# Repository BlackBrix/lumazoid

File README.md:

# Lumazoid

Firmware for the Lumazoid realtime music visualizer board from nootropic design.
Detailed technical information about Lumazoid is at http://nootropicdesign.com/lumazoid  
  
Shop: https://nootropicdesign.com/store/product-category/led-controllers/  
  
Install libraries/ffft in your Arduino sketchbook libraries folder.

Requires the [Adafruit NeoPixel library](https://github.com/adafruit/Adafruit_NeoPixel). 
Your directory structure should look like this:

```
your_sketchbook
 |
 +--libraries
 |   |
 |   +--ffft
 |   |
 |   +--Adafruit_NeoPixel
 |
 +--Lumazoid
     |
     +--Lumazoid.h
     +--Lumazoid.ino
```

In the Arduino IDE, select board type "Arduino Uno" to upload to the Lumazoid.  
  
https://youtu.be/Vjp7iLEZsX4  
https://youtu.be/2BDE81b42Ac  
https://youtu.be/lYz1uqOQcGg  
https://youtu.be/453p5HPAYZY  
https://youtu.be/N-TBdfP13BE  
  
Forum:  
https://nootropicdesign.com/store/forums/

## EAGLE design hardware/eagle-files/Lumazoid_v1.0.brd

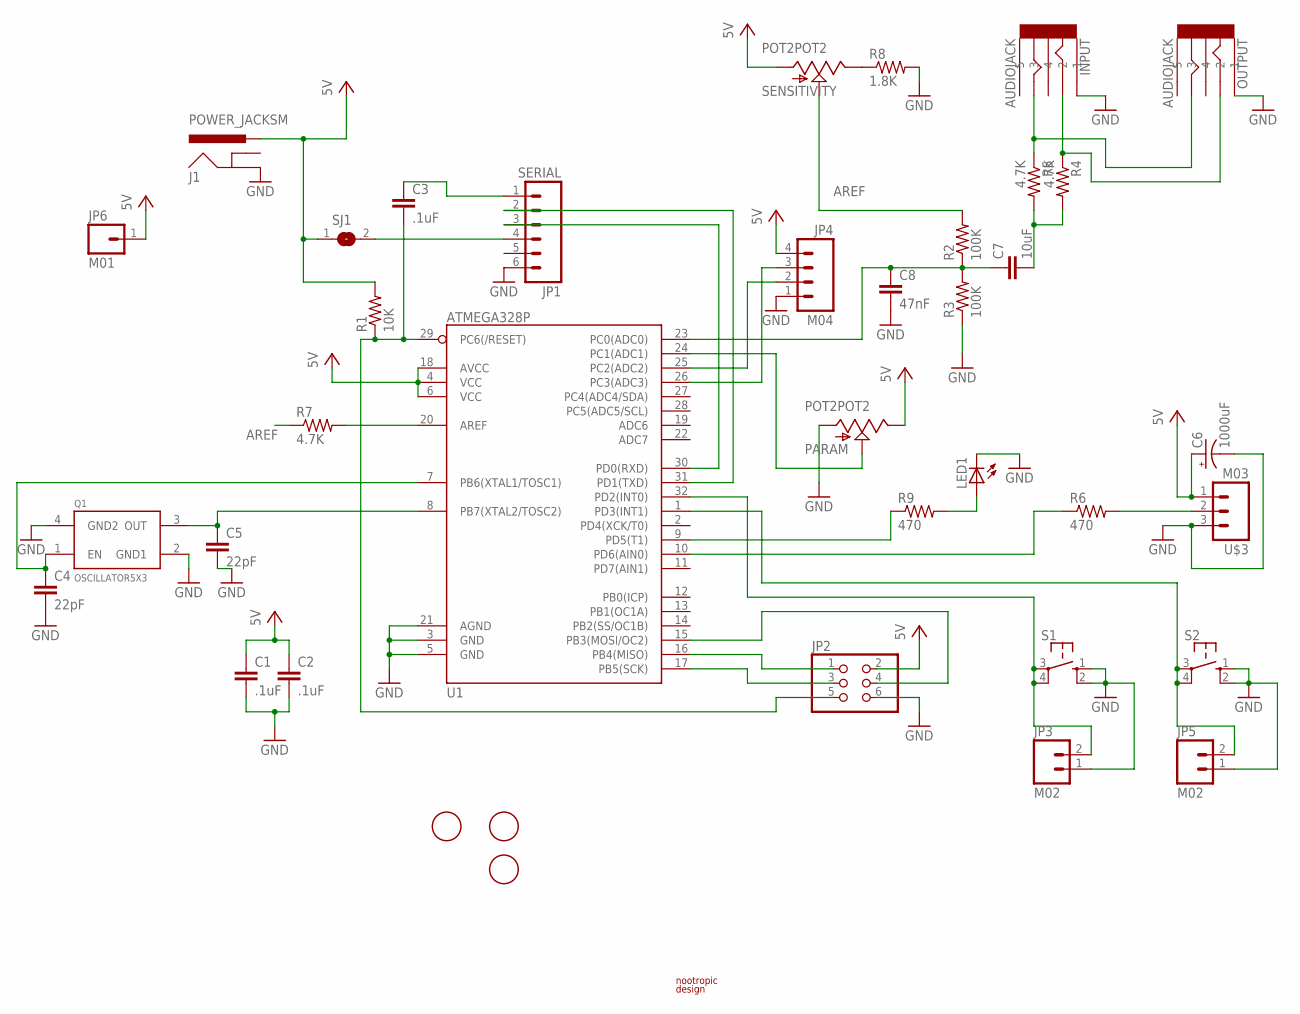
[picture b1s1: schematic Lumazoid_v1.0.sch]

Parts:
C1, C2, C3: .1uF; C0603
C4, C5: 22pF; C0603
C6: 1000uF; E5-10,5
C7: 10uF; C1206
C8: 47nF; C0603
FID1, FID2, FID3: FIDUCIAL; FIDUCIAL_1MM
INPUT: AUDIOJACK
J1: POWER_JACKSM; POWER_JACK_SM
JP1: SERIAL; 1X06
JP2: PINHD-2X3; 2X03
JP3, JP5: M02; 1X02
JP4: M04; 1X04
JP6: M01; 1X01
LED1: LEDCHIPLED_0805; CHIPLED_0805
OUTPUT: AUDIOJACK
PARAM: POT2POT2; ALPS_POT
Q1: OSCILLATOR5X3; CRYSTAL-SMD-5X3
R1: 10K; R0603
R2, R3: 100K; R0603
R4, R5, R7: 4.7K; R0603
R6, R9: 470; R0603
R8: 1.8K; R0603
S1, S2: SWITCH-TACT6MMSMT-J; DTSM-6-JBEND
SENSITIVITY: POT2POT2; ALPS_POT
SJ1: SJ
U1: ATMEGA328P; TQFP32-08
U$1: LOGO; LOGO_SMALL
U$3: M03; 1X03

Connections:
A0: C7.1, C8.1, R2.1, R3.2, U1.23 (PC0(ADC0))
A1: PARAM.P$2 (2), U1.24 (PC1(ADC1))
A2: JP4.2, U1.25 (PC2(ADC2))
A3: JP4.3, U1.26 (PC3(ADC3))
AREF: R2.2, R7.1, SENSITIVITY.P$2 (2)
D1: JP5.2, S2.3, S2.4 (P1), U1.1 (PD3(INT1))
D2: JP3.2, S1.3, S1.4 (P1), U1.32 (PD2(INT0))
DTR: C3.1, JP1.1
GND: C1.2, C2.2, C4.2, C5.2, C6.-, C8.2, INPUT.1, J1.GND, JP1.6, JP2.6, JP3.1, JP4.1, JP5.1, LED1.C, OUTPUT.1, PARAM.P$1 (1), Q1.2 (GND1), Q1.4 (GND2), R3.1, R8.2, S1.1 (S), S1.2 (S1), S2.1 (S), S2.2 (S1), U1.3 (GND), U1.5 (GND), U1.21 (AGND), U$3.3 (4)
MISO: JP2.1, U1.16 (PB4(MISO))
MOSI: JP2.4, U1.15 (PB3(MOSI/OC2))
unnamed: R6.1, U1.10 (PD6(AIN0))
unnamed: R6.2, U$3.2 (3)
unnamed: INPUT.2, OUTPUT.2, R4.1
unnamed: C5.1, Q1.3 (OUT), U1.8 (PB7(XTAL2/TOSC2))
unnamed: INPUT.3, OUTPUT.3, R5.1
unnamed: C4.1, Q1.1 (EN), U1.7 (PB6(XTAL1/TOSC1))
unnamed: R9.1, U1.9 (PD5(T1))
unnamed: LED1.A, R9.2
unnamed: JP1.4, SJ1.2
unnamed: C7.2, R4.2, R5.2
unnamed: R7.2, U1.20 (AREF)
unnamed: R8.1, SENSITIVITY.P$3 (3)
RESET: C3.2, JP2.5, R1.1, U1.29 (PC6(/RESET))
RX: JP1.3, U1.30 (PD0(RXD))
SCK: JP2.3, U1.17 (PB5(SCK))
TX: JP1.2, U1.31 (PD1(TXD))
VCC: C1.1, C2.1, C6.+, J1.PWR, JP2.2, JP4.4, JP6.1, PARAM.P$3 (3), R1.2, SENSITIVITY.P$1 (1), SJ1.1, U1.4 (VCC), U1.6 (VCC), U1.18 (AVCC), U$3.1 (2)

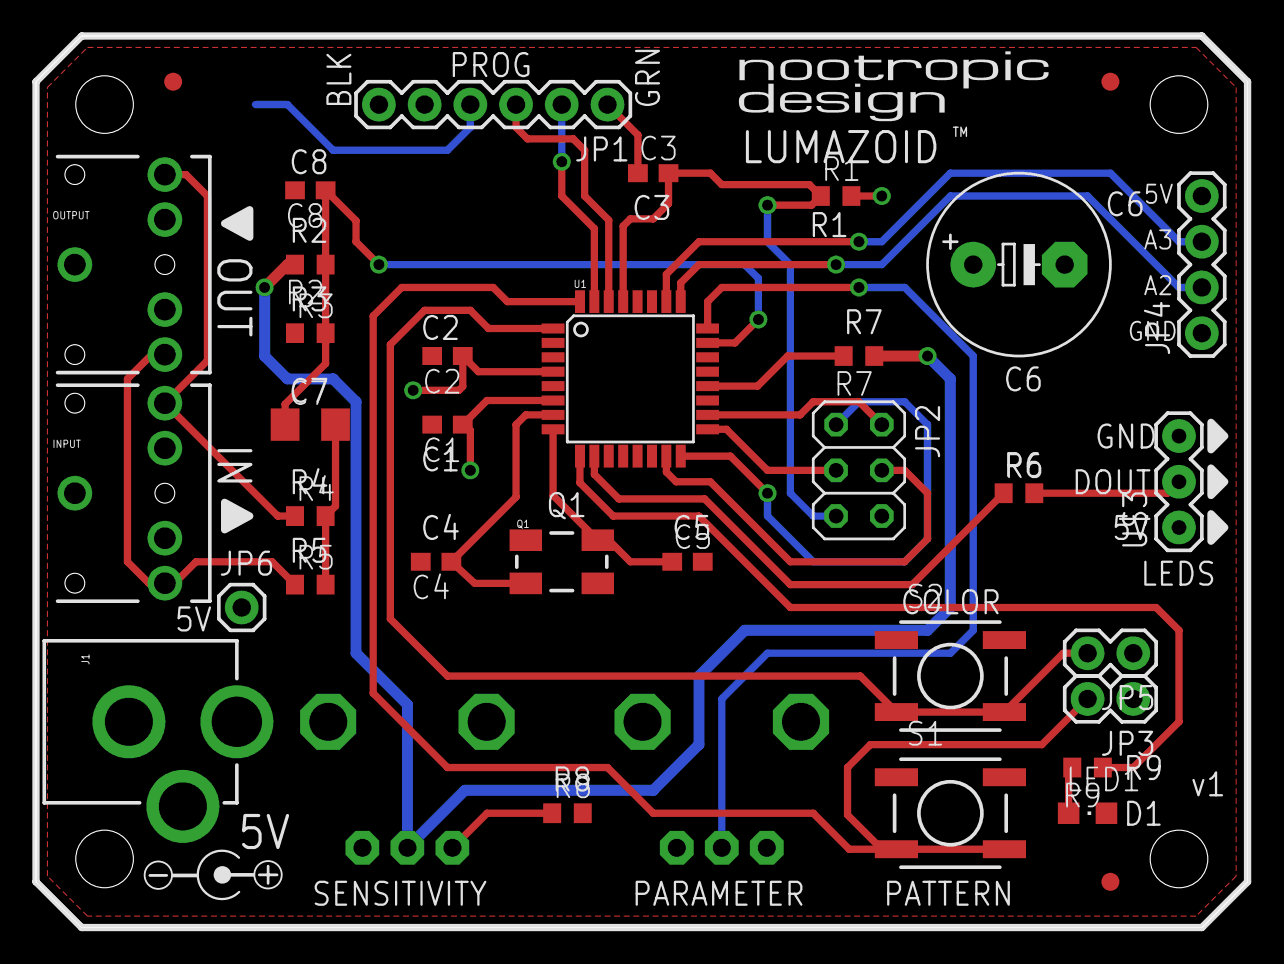
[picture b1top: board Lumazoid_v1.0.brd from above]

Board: 2 copper layers, 67.3 x 49.5 mm, 39 parts (1 on the bottom side), 28 nets.

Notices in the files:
parts and their libraries:
SparkFun-DigitalIC: Licensing: CC v3.0 Share-Alike You are welcome to use this library for commercial purposes.
